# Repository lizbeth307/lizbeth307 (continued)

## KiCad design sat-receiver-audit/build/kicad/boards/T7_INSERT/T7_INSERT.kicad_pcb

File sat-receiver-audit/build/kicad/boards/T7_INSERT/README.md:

# Вставка VBUS у кабель T7 — T7_INSERT, 41.0 × 9.0 мм — W2 PCB-SB2

**Статус: `SB2_ROUTED_MECH_FIT_OPEN_NOT_FOR_FABRICATION`.** Прогін розведення 43129454692 на 00ae328 (`sr-rx-pcb`, KiCad 10.0.7, Freerouting 2.5.0; повторне розведення на смузі wip/w2-int після злиття B2B: входи ті самі, аудит межі тепер рахує J208/J209; результат той самий, що в прогоні 43115230745 на 01d14323): DRC — помилок 0, непідключених 0, попереджень 31 (лише шовкографія: `silk_over_copper`, `silk_overlap`), `ignored_checks` порожній; аудит source-pad — 0 помилок; аудит меж — `pass`; 31 заблокований сегмент збережено; `pcb/check_boards.py` — 0 знахідок. Результат CI/моделі, не випуск у виробництво; місце в кабелі, нагрів U505 і лінія USB3 з вставкою лишаються OPEN.

## Що це

Плата всередині кабелю USB3 A–C між Q6A J5 і SSD T7 під термоусадкою (build/15 «Вставка T7: S24 і VBUS (W2 GR-4)»): розрізано лише жилу VBUS — кінець від J5 паяється в J515, кінець до T7 — у J516; J517 — відвід нерозрізаної жили GND для місцевого повернення C514–C516; екран і решта жил не розрізаються. U505 TPS2553DRVR вмикає VBUS T7 (EN_T7 з S24 через J514, X24S1-T7A), FAULT — на TP501 і до Q6A через підтяжку R516 до 3V3_Q6A.

## Розміщення й мідь

Координати — мм від лівого нижнього кута контуру, y угору; усі деталі зверху (F), знизу лише мідь.

- **x 0.3–4.1:** J517 (2.2, 2.3) і J515 (2.2, 6.7) — майданчики 0.75 мм² (отвір 1.6) кінця J5.
- **x 5–17:** C515 / C514 на вході, U505 (9.6, 5.0) з поворотом 180° (IN до J515, OUT до J516), над ним R515 (EN), TP501 і R516 (FAULT), праворуч R514 (RILIM), знизу R517 (розряд VBUS_T7).
- **x 16.5–20.3:** J516 (18.4, 4.35) — кінець жили до T7.
- **x 20.4–32.0:** C516 16SVPC150M (полімер D8 × L6.9, найвища деталь, 6.9 мм).
- **x 32.15–40.75:** J514 S3B-PH-K бічного входу з отвором назовні (S24).
- **Мідь:** усі сигнальні кола скриптові й заблоковані — VBUS 0.8 мм (ширина PWR2A), звужена до 0.35 мм біля виводів WSON; EN_T7 і 3V3_Q6A — по B.Cu під C516 з переходами біля R515 і J516; FAULT і ILIM — по F.Cu. Роутер з'єднує лише GND; заливки GND на обох шарах з прямим приєднанням, два перехідні отвори у відкритій площадці U505 і п'ять зшивальних.

## Тепло U505 (МОДЕЛЬ)

SLVS841G (прочитано 11.11.2026): DRV — rDS(on) ≤ 140 мОм при TJ ≤ 105 °C, RθJA 72 °C/W (плата JEDEC). При 1.5 A: P = 0.140 × 1.5² = 0.315 W, ΔT ≈ 22.7 °C → TJ ≤ 105 °C до повітря 82 °C. Плата 41 × 9 з двома шарами менша за плату JEDEC, тож це оцінка; ворота IO-01 / T — OPEN (стенд).

## Відкрито (OPEN)

- **Місце:** плата має ширину 9.0 і висоту 8.5 резерву W2 MECH-5 (layout t7_insert), але довжину 41.0 замість 21.5 — сума кортиярдів 13 деталей (≈266 мм², сума courtyard_box у `report.json`) більша за 21.5 × 9.0 (193.5 мм²); механіка вибирає місце вздовж кабелю T7 (траса кабелю не модельована, J511 interface_open). У `contract-proposal.json` розташування в корпусі немає.
- E5_VBUS_J5 / E5_VBUS_T7 відсутні в `tools/assembly_data.py` NET_CURRENT (власник — лінія GR-1/INT), тож `check_boards` перевіряє їх як SIG.
- Термоусадки й стяжки для вставки в закупівлі немає; переріз жил VBUS/GND обраного кабелю T7 не опубліковано (E5-05, вимір).

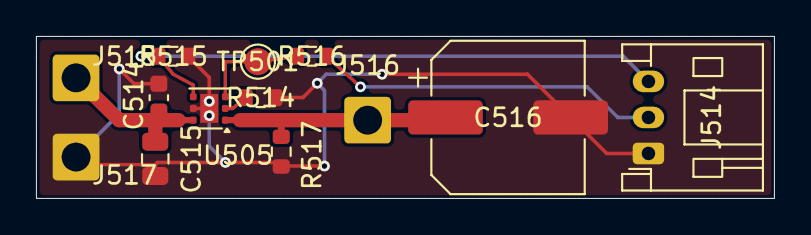
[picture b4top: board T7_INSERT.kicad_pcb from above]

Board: 2 copper layers, 41.0 x 9.0 mm, 13 parts (0 on the bottom side), 7 nets.

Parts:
C514: 100nF X7R 10V; C_0603_1608Metric
C515: 4.7uF X7R 10V; C_0805_2012Metric
C516: 150uF 10V low-ESR; CP_Elec_8x6.9
J514: X24S1-T7A: JST PH 3, боковий вхід, S24; JST_PH_S3B-PH-K_1x03_P2.00mm_Horizontal
J515: Майданчик VBUS-жили кабелю T7: вхід від Q6A J5; SolderWire-0.75sqmm_1x01_D1.25mm_OD2.3mm
J516: Майданчик VBUS-жили кабелю T7: вихід до T7; SolderWire-0.75sqmm_1x01_D1.25mm_OD2.3mm
J517: Майданчик відводу GND-жили кабелю T7; SolderWire-0.75sqmm_1x01_D1.25mm_OD2.3mm
R514: RILIM TBD (start 15.8k 1%); R_0603_1608Metric
R515: 100k; R_0603_1608Metric
R516, R517: 10k; R_0603_1608Metric
TP501: T7 FAULT_N test point; TestPoint_Pad_D1.5mm
U505: TPS2553DRVR; WSON-6-1EP_2x2mm_P0.65mm_EP1x1.6mm

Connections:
3V3_Q6A: J514.2, R516.2
E5_FAULT_T7: R516.1, TP501.1, U505.3
E5_U505_ILIM: R514.1, U505.2
E5_VBUS_J5: C514.1, C515.1, J515.1, U505.6
E5_VBUS_T7: C516.1, J516.1, R517.1, U505.1
EN_T7: J514.3, R515.1, U505.4
GND: C514.2, C515.2, C516.2, J514.1, J517.1, R514.2, R515.2, R517.2, U505.5, U505.7
